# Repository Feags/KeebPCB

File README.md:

# KeebPCB
 Trying to make keyboard

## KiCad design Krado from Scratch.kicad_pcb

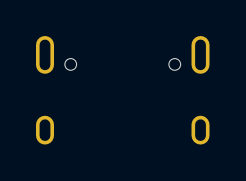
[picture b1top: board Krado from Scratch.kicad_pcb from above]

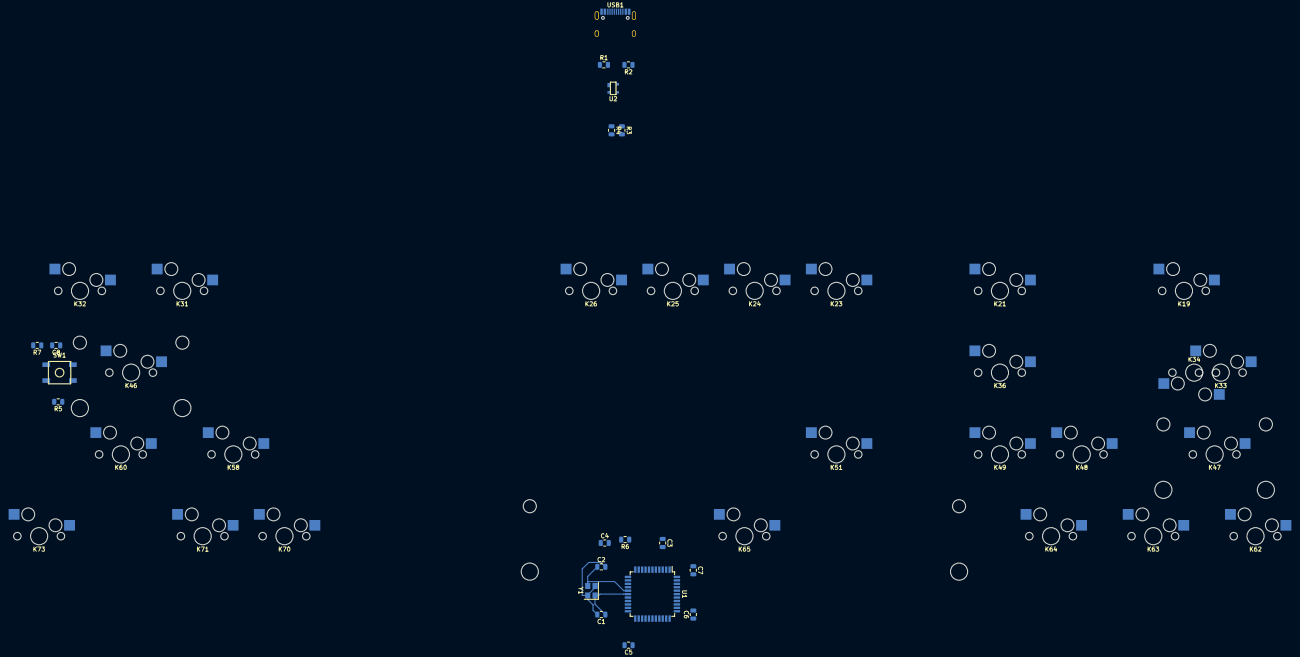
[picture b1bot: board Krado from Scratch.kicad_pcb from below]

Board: 2 copper layers, 46 parts (20 on the bottom side), 26 nets.

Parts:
C1, C2, C8: 22pF; C_0805_2012Metric
C3: 1uF; C_0805_2012Metric
C4, C5, C6: 0.1uF; C_0805_2012Metric
C7: 10uF; C_0805_2012Metric
K19: TAB; MXOnly-1.5U-Hotswap
K21: W; MXOnly-1U-Hotswap
K23: R; MXOnly-1U-Hotswap
K24: T; MXOnly-1U-Hotswap
K25: Y; MXOnly-1U-Hotswap
K26: U; MXOnly-1U-Hotswap
K31: }]; MXOnly-1U-Hotswap
K32: BAR-BACKSLASH; MXOnly-1U-Hotswap
K33: STEP_CAPS; MXOnly-1U-Hotswap
K34: CAPS; MXOnly-1.75U-Hotswap
K36: S; MXOnly-1U-Hotswap
K45: '; MXOnly-1U-Hotswap
K46: ENTER; MXOnly-2.25U-Hotswap
K47: L_SHIFT; MXOnly-2.25U-Hotswap
K48: Z; MXOnly-1U-Hotswap
K49: X; MXOnly-1U-Hotswap
K51: V; MXOnly-1U-Hotswap
K58: R_SHIFT_1.75U; MXOnly-1.75U-Hotswap
K60: UP; MXOnly-1U-Hotswap
K62: L_CTRL; MXOnly-1.25U-Hotswap
K63: L_GUI; MXOnly-1.25U-Hotswap
K64: L_ALT; MXOnly-1.25U-Hotswap
K65: SPACE; MXOnly-6.25U-Hotswap
K70: R_CTRL; MXOnly-1U-Hotswap
K71: LEFT; MXOnly-1U-Hotswap
K73: RIGHT; MXOnly-1U-Hotswap
R1, R2: 5.1k; R_0805_2012Metric
R3, R4: 22; R_0805_2012Metric
R5, R6: 10k; R_0805_2012Metric
R7: 330; R_0805_2012Metric
SW1: SW_Push; SKQG-1155865
U1: ATmega32U4-AU; TQFP-44_10x10mm_P0.8mm
U2: PRTR5V0U2X; SOT143B
USB1: HRO-TYPE-C-31-M-12
Y1: 16MHz; Crystal_SMD_3225-4Pin_3.2x2.5mm

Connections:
+5V: C4.1, C5.1, C6.1, C7.1, R5.1, U1.2, U1.7, U1.14, U1.24, U1.34, U1.44
COL0: K62.1, U1.29
COL1: K19.1, K33.1, K34.1, K47.1, K63.1, U1.30
COL2: K48.1, K64.1, U1.12
COL3: K21.1, K36.1, K49.1, U1.31
COL5: K23.1, K51.1, U1.18
COL6: K24.1, K65.1, U1.19
COL7: K25.1, U1.20
COL8: K26.1, U1.21
COL12: K58.1, K70.1, U1.27
COL13: K31.1, K46.1, K71.1, U1.41
COL14: K32.1, K60.1, U1.40
COL15: K73.1, U1.39
D+: R4.1, R4.2, U1.4, U2.2, USB1.6, USB1.8
D-: R3.1, R3.2, U1.3, U2.3, USB1.5, USB1.7
GND: C1.2, C2.2, C3.2, C4.2, C5.2, C6.2, C7.2, R1.1, R2.1, R6.1, R7.2, U1.5, U1.15, U1.23, U1.35, U1.43, U2.1, USB1.1, USB1.12, USB1.13, Y1.2, Y1.4
unnamed: C1.1, U1.17, Y1.1
unnamed: C2.1, U1.16, Y1.3
unnamed: C3.1, U1.6
unnamed: C8.2, R7.1, SW1.1
unnamed: K33.2, K34.2
unnamed: R1.2, USB1.4
unnamed: R2.2, USB1.10
unnamed: R6.2, U1.33
RST: C8.1, R5.2, SW1.2, U1.13
VCC: U2.4, USB1.2, USB1.11

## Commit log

2021-04-13 New Project
2021-04-13 MCU complete
2021-04-13 USB-C Added
2021-04-13 MATRI
2021-04-13 Matrix Fixed
2021-04-13 Matrix Named
2021-04-14 PCB Generated
2021-04-14 PCB Switches Layout
2021-04-14 PCB Mapped
2021-04-14 PCB Cleaned Up
2021-04-14 Tracing
2021-04-14 Renamed Ref
2021-04-14 Various Fixes
